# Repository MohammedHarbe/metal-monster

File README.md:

<p align="center">
  <b>Griffen by Vanguards. An engineering journey since 2023.</b><br>
  Mechanical fabrication, custom electronics, and ESP-NOW control.
</p>

<p align="center">
  <a href="mechanical/README.md">Mechanical</a> &nbsp;·&nbsp;
  <a href="firmware/README.md">Firmware</a> &nbsp;·&nbsp;
  <a href="electrical/README.md">Electrical</a> &nbsp;·&nbsp;
  <a href="docs/history/README.md">Our story</a> &nbsp;·&nbsp;
  <a href="docs/history/videos/first-integrated-operation.mp4">Watch the first run</a>
</p>

---

## Meet Griffen

We are **Vanguards**, and we have been working on **Griffen since 2023**: a manually controlled robot built for robot-versus-robot competition. Two wheelchair motors move the base, while a starter motor powers its metal spinner. A handheld remote communicates with an onboard **ESP32 DevKitC V4** over **ESP-NOW**.

<table>
<tr>
<td width="50%" align="center"><br><b>The painted robot</b></td>
<td width="50%" align="center"><br><b>Before paint and later modifications</b></td>
</tr>
</table>

<p align="center">
  <a href="docs/history/videos/first-integrated-operation.mp4"><b>▶ Watch or download our first integrated-operation video</b></a><br>
  <sub>A milestone identified by the team: the first time the robot worked together as a complete system.</sub>
</p>

The repository retains its original `metal-monster` name; **Griffen** is the robot and **Vanguards** is the team.

[Download the supplied PCB logo DXF](docs/assets/Logo_for_PCB.DXF).

## Explore the build

| Area | What you will find | Availability |
| :--- | :--- | :--- |
| **[Mechanical](mechanical/README.md)** | Robot photos, motor references, and [remote PCB CAD](mechanical/remote/README.md) | Remote CAD included · chassis CAD to come |
| **[Firmware](firmware/README.md)** | Separate ESP-NOW remote and receiver sketches, setup notes, and known issues | Source included |
| **[Robot receiver](electrical/receiver/README.md)** | KiCad project, schematic, PCB, Gerbers, drill files, and renders | Design package included |
| **[Handheld remote](electrical/remote/README.md)** | KiCad review package, PCB models, Gerbers, schematic PDFs, and renders | Design packages included |
| **[Project history](docs/history/README.md)** | Early electronics, team photo, and first-operation video | Media included |

## Two circuits. One robot.

<table>
<tr><td width="50%" align="center"><b>HANDHELD REMOTE</b><br><sub>Manual inputs → ESP-NOW commands</sub></td><td width="50%" align="center"><b>ONBOARD RECEIVER</b><br><sub>ESP-NOW commands → motor and relay control</sub></td></tr>
<tr>
<td align="center"></td>
<td align="center"></td>
</tr>
<tr><td>The handheld remote reads joystick and switch inputs. Its supplied KiCad review package, mechanical exports, Gerbers, PDFs, and renders are now included.</td><td>The supplied custom PCB hosts the ESP32 DevKitC V4 and interfaces with the drive controller and spinner relay.</td></tr>
</table>

## Hardware at a glance

| | Drive system | Spinner system |
| :--- | :--- | :--- |
| **Motor** | Two wheelchair motors | Starter motor driving a metal spinner |
| **Control** | MDD20A motor driver | BC338 transistor stage and relay |
| **Battery** | **24 V · 20 Ah** lithium-ion | **11.1 V · 3S · 10.4 Ah** LiPo |
| **Reference** | [Drive battery](electrical/receiver/images/drive-battery-reference.png) | [Battery listing](electrical/receiver/images/starter-battery-listing.png) |

The receiver uses an **ESP32 DevKitC V4**. Its spinner GPIO drives a **5 V relay coil** through the BC338 interface; the relay contacts switch starter-motor power directly. The coil supply and motor supply are separate specifications.

<details>
<summary><b>Specification sources and remaining checks</b></summary>

- The drive battery's 24 V, 20 Ah rating is owner-reported. Its cell count and full-charge voltage are not documented.
- The spinner battery listing specifies 11.1 V, 3S, 10,400 mAh, and 40C. These are listing specifications, not measured performance.
- The wheelchair-motor reference image is labelled MY1016Z, 24 V, 250 W; the installed motors' exact model and nameplate ratings remain unconfirmed.
- Starter current, relay contact suitability, and PCB current-carrying capacity remain unverified. See the [receiver documentation](electrical/receiver/README.md).

</details>

## Vanguards · Built together since 2023

From the early receiver and handheld remote to the assembled robot, this repository brings our work into one place. The [project history](docs/history/README.md) records those stages without assigning unconfirmed dates to individual milestones.

## Start exploring

1. **Read the [firmware guide](firmware/README.md)** for the transmitter and receiver setup.
2. **Open the [receiver KiCad project](electrical/receiver/source/Reciever_metal_monster.kicad_pro)** with its accompanying schematic and PCB.
3. **Browse the [manufacturing package](electrical/receiver/manufacturing/)** for Gerber and drill exports.
4. **Check the documented issues** before building or testing.

<details>
<summary><b>Repository map</b></summary>

```text
metal-monster/
├── mechanical/             Robot references and remote PCB CAD
├── firmware/
│   ├── esp-now/
│   │   ├── trans/          Handheld remote sketch
│   │   └── reciver/        Robot receiver sketch
│   └── legacy/             Original unused SBUS sketch
├── electrical/
│   ├── receiver/
│   │   ├── source/         Editable KiCad files
│   │   ├── manufacturing/  Gerbers, drills, and original archive
│   │   ├── schematics/     Schematic PDF
│   │   ├── pcb/            PCB PDF
│   │   └── images/         Board and component references
│   └── remote/             Handheld circuit documentation
└── docs/
    ├── assets/             README artwork
    └── history/            Prototype photos, team, and video
```

</details>

### Development status

**ESP-NOW is the active control system; SBUS is unused legacy material.** Existing firmware is preserved, including the transmitter's missing receiver-address declaration and direction-mapping issues. Repository documentation updates do not establish successful compilation, hardware validation, or fabrication readiness. Robot chassis CAD is still to be added; remote PCB mechanical exports and circuit design packages are now included.

---

<p align="center"><sub>VANGUARDS / GRIFFEN · MECHANICAL / ELECTRICAL / FIRMWARE · SINCE 2023</sub></p>

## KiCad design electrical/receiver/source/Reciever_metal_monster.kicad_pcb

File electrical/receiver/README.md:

# Receiver Circuit — Mobile Robot

This circuit is installed on the mobile robot and receives manual-control commands from the handheld remote over ESP-NOW.

[Electrical overview](../README.md) · [Remote circuit](../remote/README.md) · [Receiver firmware](../../firmware/esp-now/reciver/reciver.ino)

## Receiver hardware

The receiver uses an **ESP32 DevKitC V4**, confirmed by the project owner. The custom PCB provides board headers, two motor-driver signal connectors, a 5 V relay-driver stage, and relay contact terminals.

### Supplied files

- [PCB logo artwork (DXF)](../../docs/assets/Logo_for_PCB.DXF)

- [Editable KiCad project](source/Reciever_metal_monster.kicad_pro)
- [Editable schematic](source/Reciever_metal_monster.kicad_sch)
- [Editable PCB](source/Reciever_metal_monster.kicad_pcb)
- [Original KiCad archive](source/Reciever_metal_monster_PCB.rar)
- [Manufacturing archive](manufacturing/METAL_MONSTER_RECIEVER_GBR.rar)
- [Extracted manufacturing files](manufacturing/METAL_MONSTER_RECIEVER_GBR)

- [Receiver schematic](schematics/Reciver_pdf.pdf)
- [PCB layout export](pcb/PCB_reciver.pdf)
- [Top PCB render](images/Reciever_metal_monster.png)
- [Angled PCB render](images/Reciever_metal_monster_2.png)
- [Underside PCB render](images/Reciever_metal_monster_3.png)
- [Starter motor reference photo](images/starter-motor-reference.jpg)

The photo is a user-supplied reference, not an identified manufacturer part or a verified image of the installed assembly. Original filenames are retained for the design exports. Editable KiCad sources and Gerber/drill exports are now included. A component BOM has not been supplied.

## Spinner relay interface

The supplied schematic shows:

| Item | Value / role |
| --- | --- |
| Control net | `Spiner_ESP` (original schematic spelling) |
| Transistor | BC338, low-side coil switch |
| Base series resistor | 470 ohms |
| Base pull-down | 10 kilohms to ground |
| Relay | SPDT, coil connected to +5 V |
| Coil diode | 1N4007 across the coil |
| Indicator | LED with 220-ohm series resistor |
| Contact outputs | COM, NO, NC |

Control path:

```text
ESP32 spinner GPIO -> 470-ohm resistor -> BC338 base
+5 V -> relay coil -> BC338 collector/emitter -> GND
Relay contacts -> starter motor power circuit (direct switching, owner-confirmed)
```

The transistor provides coil-current drive; the ESP32 GPIO does not supply the coil's 5 V power. Based on the schematic, a HIGH control signal turns on the transistor and energizes the relay; LOW releases it. The 1N4007 is across the relay coil, not across the external starter motor.

The project owner confirms that the relay contacts switch motor power directly, rather than energizing the starter solenoid. External battery wiring and the selected COM/NO/NC connection are not shown in the supplied schematic. The team reports a separate 11.1 V (3S), 10.4 Ah LiPo supply for the starter motor. The relay's 5 V rating describes its coil supply.

**Load capacity is unverified:** the PDF names a generic relay; the editable source uses a SANYOU SRD-series symbol/footprint and does not specify its DC motor-load contact rating, starter inrush/stall current, or PCB current-carrying capacity. The presence of a coil driver alone does not establish that the contact path is suitable for switching this starter motor.

## ESP-NOW firmware GPIO reference

These values come from the preserved sketches. They are GPIO numbers, not the 1-19 header-position labels in the schematic.

| Receiver signal | GPIO |
| --- | --- |
| Motor 1 PWM | 12 |
| Motor 1 DIR | 22 |
| Motor 2 PWM | 13 |
| Motor 2 DIR | 18 |
| Spinner control | 16 |

The receiver sets GPIO 16 HIGH when `swit == 0`; boot setup and the 500 ms packet timeout set it LOW. This matches the intended active-high transistor stage in the schematic, subject to verifying board orientation and actual wiring.

The drawing uses two numbered 19-pin headers. Verify their orientation against the actual DevKitC V4 before treating header numbers as GPIO assignments. [Espressif board and pin-layout reference](https://docs.espressif.com/projects/esp-dev-kits/en/latest/esp32/esp32-devkitc/user_guide.html).

## Information still needed

Add the relay part number and ratings, starter specifications, actual motor-power wiring, protection and power-distribution details, and a component BOM. Record the physical motor 1/motor 2 sides and verified forward direction. Mechanical CAD belongs in the mechanical section.

These documents describe supplied evidence and owner-confirmed configuration; they do not certify PCB fabrication, relay load capacity, or bench operation.

## Opening the source and manufacturing package

Open the `.kicad_pro` file in `source/`, keeping the schematic and PCB beside it. The board references KiCad 9 standard 3D model library paths (`KICAD9_3DMODEL_DIR`). Original archives are preserved alongside the extracted files.

The manufacturing archive contains 10 Gerber layers, a Gerber job file, and separate plated/non-plated drill files (13 files total). Archive extraction and file presence were checked; ERC, DRC, fabrication readiness, and consistency between source and manufacturing exports have not been validated.

## Robot drive and power configuration

The team identifies the base motors as wheelchair motors controlled by an MDD20A motor driver, powered by a reported 24 V, 20 Ah lithium-ion battery. A separate reported 11.1 V (3S), 10.4 Ah LiPo battery powers the starter motor driving the metal spinner for robot-versus-robot competition.

These are owner-reported hardware details, not a completed compatibility assessment. Drive-battery cell count and full-charge voltage, motor nameplate details, current measurements, and the receiver/relay 5 V supply arrangement still need documentation. The supplied schematic does not show the complete two-battery power wiring.

## Earlier hardware

See the [old receiver setup](../../docs/history/README.md#early-receiver-setup) for the earlier enclosure-mounted prototype. The design files in this folder document the supplied receiver PCB.

## Battery references

- [Wheel-motor battery](images/drive-battery-reference.png): 24 V, 20 Ah lithium-ion, confirmed by the owner.
- [Starter battery reference](images/starter-battery-reference.png).
- [Starter battery listing](images/starter-battery-listing.png): 11.1 V, 3S, 10,400 mAh (10.4 Ah), 40C; listed dimensions 170 × 55 × 27 mm. Listing ratings have not been independently measured. This supersedes the earlier 12 V, 7.5 Ah description.

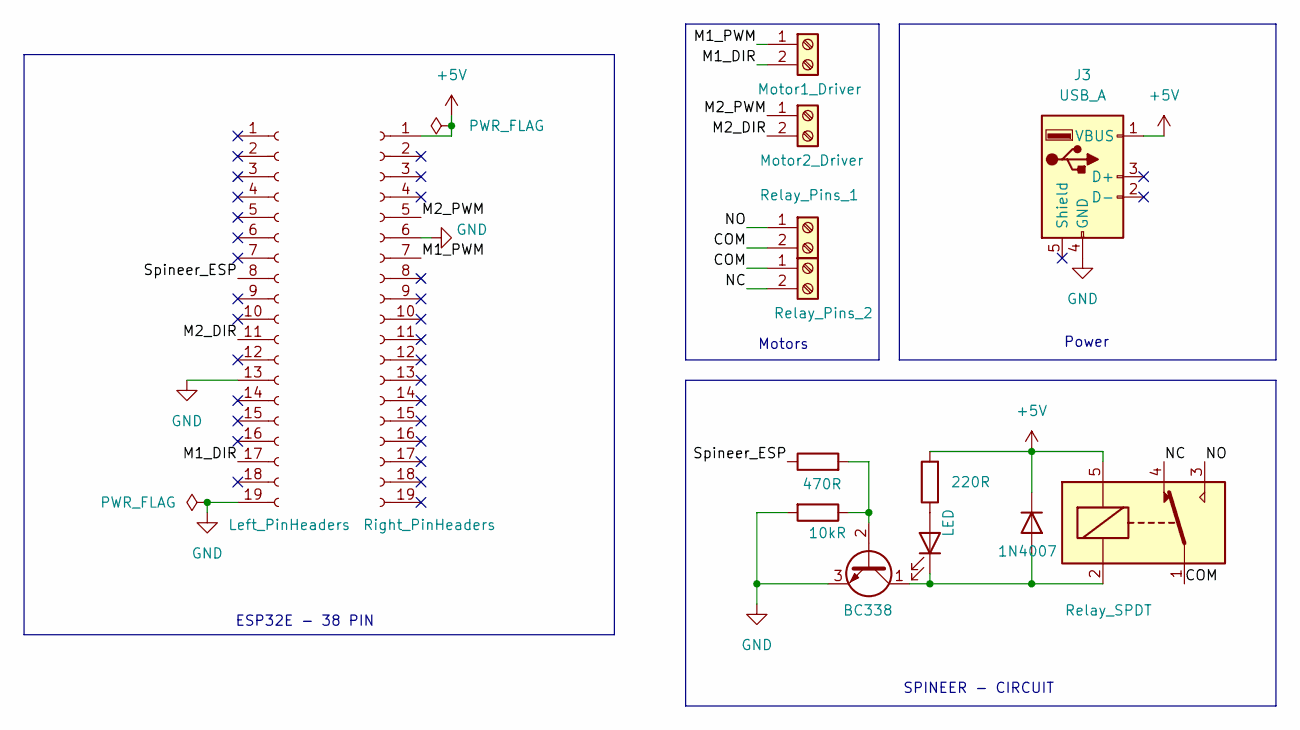
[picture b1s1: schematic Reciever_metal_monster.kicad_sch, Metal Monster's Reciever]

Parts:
D1: LED; LED_D10.0mm
D2: 1N4007; D_DO-41_SOD81_P10.16mm_Horizontal
F1: Left_PinHeaders; PinSocket_1x19_P2.54mm_Vertical
F2: Right_PinHeaders; PinSocket_1x19_P2.54mm_Vertical
J1: Motor1_Driver; TerminalBlock_Wuerth_691311400102_P7.62mm
J2: Motor2_Driver; TerminalBlock_Wuerth_691311400102_P7.62mm
J3: USB_A; USB_A_Molex_67643_Horizontal
J5: Relay_Pins_1; TerminalBlock_Wuerth_691311400102_P7.62mm
J6: Relay_Pins_2; TerminalBlock_Wuerth_691311400102_P7.62mm
K1: Relay_SPDT; Relay_SPDT_SANYOU_SRD_Series_Form_C
Q1: BC338; TO-92_Inline_Wide
R1: 470R; R_Axial_DIN0207_L6.3mm_D2.5mm_P7.62mm_Horizontal
R2: 10kR; R_Axial_DIN0207_L6.3mm_D2.5mm_P7.62mm_Horizontal
R3: 220R; R_Axial_DIN0207_L6.3mm_D2.5mm_P7.62mm_Horizontal

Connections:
+5V: D2.1 (K), F2.1, J3.1 (VBUS), K1.5, R3.2
/COM: J5.2, J6.1, K1.1
/M1_DIR: F1.17, J1.2
/M1_PWM: F2.7, J1.1
/M2_DIR: F1.11, J2.2
/M2_PWM: F2.5, J2.1
/NC: J6.2, K1.4
/NO: J5.1, K1.3
/Spineer_ESP: F1.8, R1.1
GND: F1.13, F1.19, F2.6, J3.4 (GND), Q1.3 (E), R2.2
unnamed: D1.2 (A), R3.1
unnamed: D1.1 (K), D2.2 (A), K1.2, Q1.1 (C)
unnamed: Q1.2 (B), R1.2, R2.1

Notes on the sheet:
Motors
SPINEER - CIRCUIT
ESP32E - 38 PIN
Power

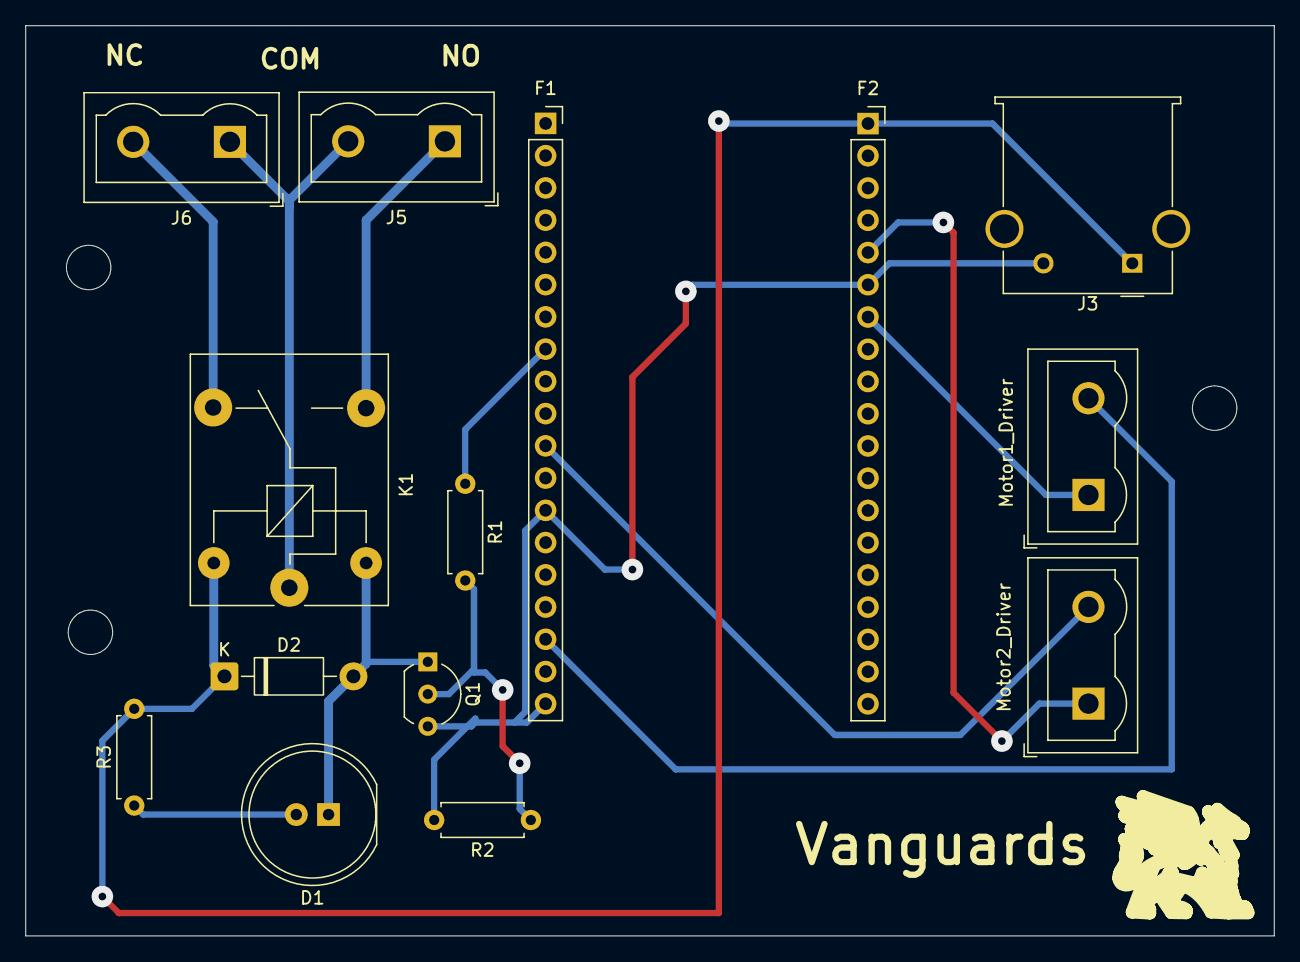
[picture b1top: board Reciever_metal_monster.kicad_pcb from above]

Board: 2 copper layers, 98.4 x 71.7 mm, 14 parts (0 on the bottom side), 13 nets.
